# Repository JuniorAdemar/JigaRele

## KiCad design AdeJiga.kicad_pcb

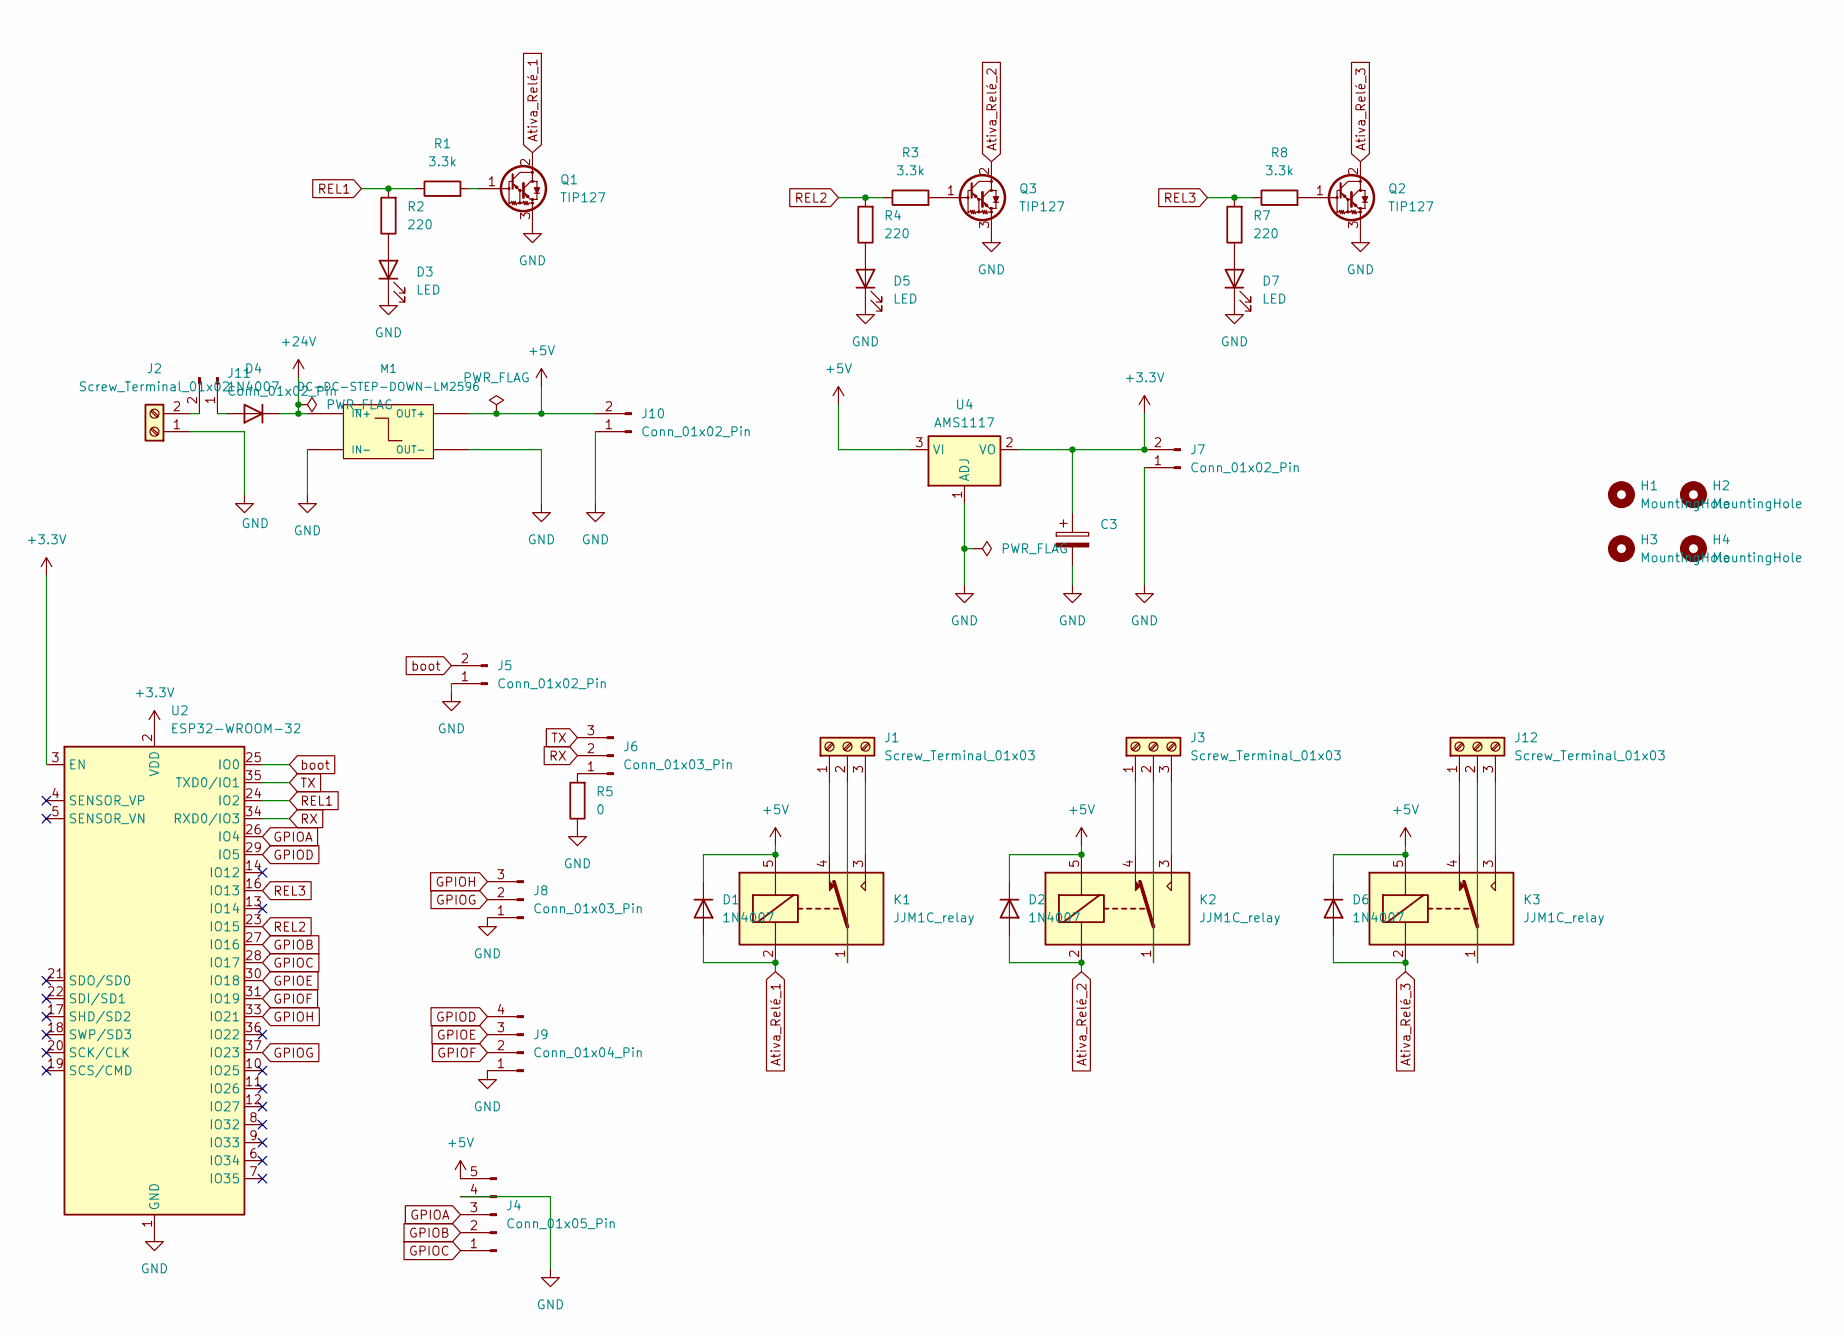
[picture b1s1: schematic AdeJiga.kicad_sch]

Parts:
C3: 220uF; CP_Radial_D6.3mm_P2.50mm
D1, D2, D4, D6: 1N4007; D_DO-41_SOD81_P10.16mm_Horizontal
D3, D5, D7: LED; LED_D5.0mm_Clear
H1, H2, H3, H4: MountingHole; MountingHole_3.2mm_M3_DIN965
J1, J3, J12: Screw_Terminal_01x03; TerminalBlock_MetzConnect_Type011_RT05503HBWC_1x03_P5.00mm_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
J2: Screw_Terminal_01x02; TerminalBlock_MetzConnect_Type011_RT05502HBWC_1x02_P5.00mm_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
J4: Conn_01x05_Pin; PinSocket_1x05_P2.54mm_Vertical
J5, J7, J10, J11: Conn_01x02_Pin; PinHeader_1x02_P2.54mm_Vertical
J6, J8: Conn_01x03_Pin; PinHeader_1x03_P2.54mm_Vertical
J9: Conn_01x04_Pin; PinHeader_1x04_P2.54mm_Vertical
K1, K2, K3: JJM1C_relay
M1: DC-DC-STEP-DOWN-LM2596
Q1, Q2, Q3: TIP127; TO-220-3_Vertical
R1, R3, R8: 3.3k; R_Axial_DIN0207_L6.3mm_D2.5mm_P10.16mm_Horizontal
R2, R4, R7: 220; R_Axial_DIN0207_L6.3mm_D2.5mm_P10.16mm_Horizontal
R5: 0; R_Axial_DIN0204_L3.6mm_D1.6mm_P5.08mm_Vertical
U2: ESP32-WROOM-32
U4: AMS1117; SOT-223-3_TabPin2

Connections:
+3.3V: C3.1, J7.2, U2.2 (VDD), U2.3 (EN), U4.2 (VO)
+5V: D1.1 (K), D2.1 (K), D6.1 (K), J4.5, J10.2, K1.5, K2.5, K3.5, M1.OUT+, U4.3 (VI)
+24V: D4.1 (K), M1.IN+
Ativa_Relé_1: D1.2 (A), K1.2, Q1.2 (C)
Ativa_Relé_2: D2.2 (A), K2.2, Q3.2 (C)
Ativa_Relé_3: D6.2 (A), K3.2, Q2.2 (C)
GND: C3.2, D3.1 (K), D5.1 (K), D7.1 (K), J2.1, J4.4, J5.1, J7.1, J8.1, J9.1, J10.1, M1.IN-, M1.OUT-, Q1.3 (E), Q2.3 (E), Q3.3 (E), R5.1, U2.1 (GND), U2.15 (GND), U2.38 (GND), U2.39 (GND), U4.1 (ADJ)
GPIOA: J4.3, U2.26 (IO4)
GPIOB: J4.2, U2.27 (IO16)
GPIOC: J4.1, U2.28 (IO17)
GPIOD: J9.4, U2.29 (IO5)
GPIOE: J9.3, U2.30 (IO18)
GPIOF: J9.2, U2.31 (IO19)
GPIOG: J8.2, U2.37 (IO23)
GPIOH: J8.3, U2.33 (IO21)
unnamed: D3.2 (A), R2.1
unnamed: D4.2 (A), J11.1
unnamed: D5.2 (A), R4.1
unnamed: D7.2 (A), R7.1
unnamed: J1.1, K1.4
unnamed: J1.2, K1.1
unnamed: J1.3, K1.3
unnamed: J3.1, K2.4
unnamed: J3.2, K2.1
unnamed: J3.3, K2.3
unnamed: J6.1, R5.2
unnamed: J2.2, J11.2
unnamed: J12.1, K3.4
unnamed: J12.2, K3.1
unnamed: J12.3, K3.3
unnamed: Q1.1 (B), R1.2
unnamed: Q2.1 (B), R8.2
unnamed: Q3.1 (B), R3.2
REL1: R1.1, R2.2, U2.24 (IO2)
REL2: R3.1, R4.2, U2.23 (IO15)
REL3: R7.2, R8.1, U2.16 (IO13)
RX: J6.2, U2.34 (RXD0/IO3)
TX: J6.3, U2.35 (TXD0/IO1)
boot: J5.2, U2.25 (IO0)

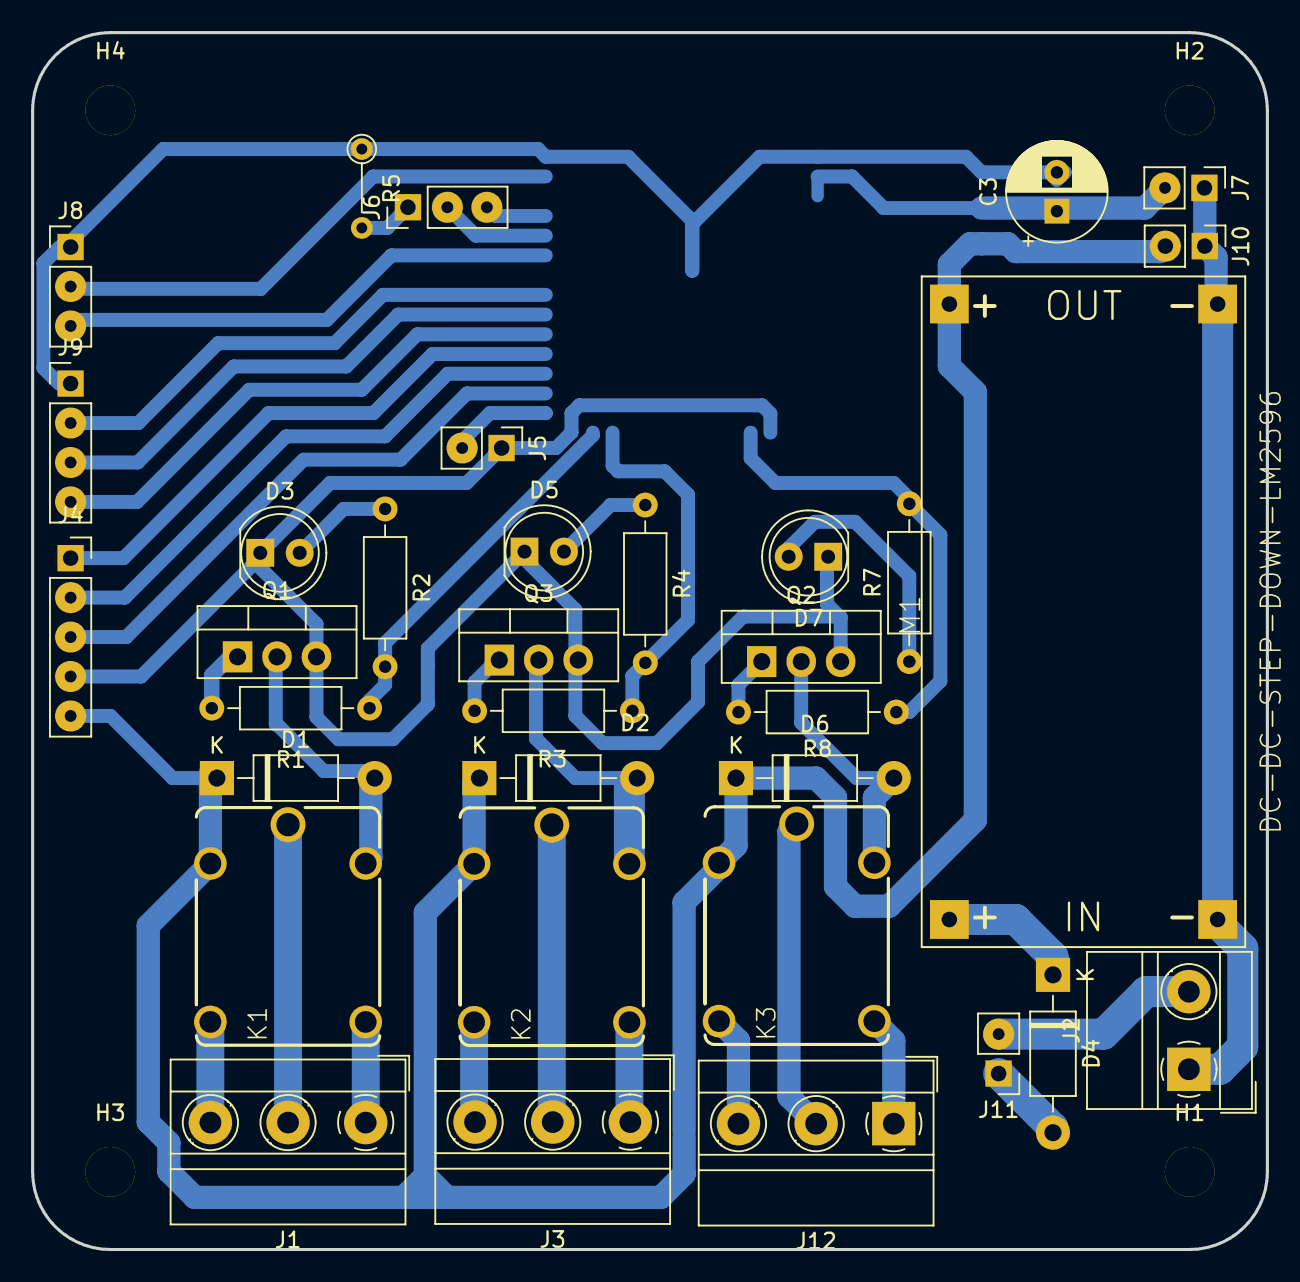
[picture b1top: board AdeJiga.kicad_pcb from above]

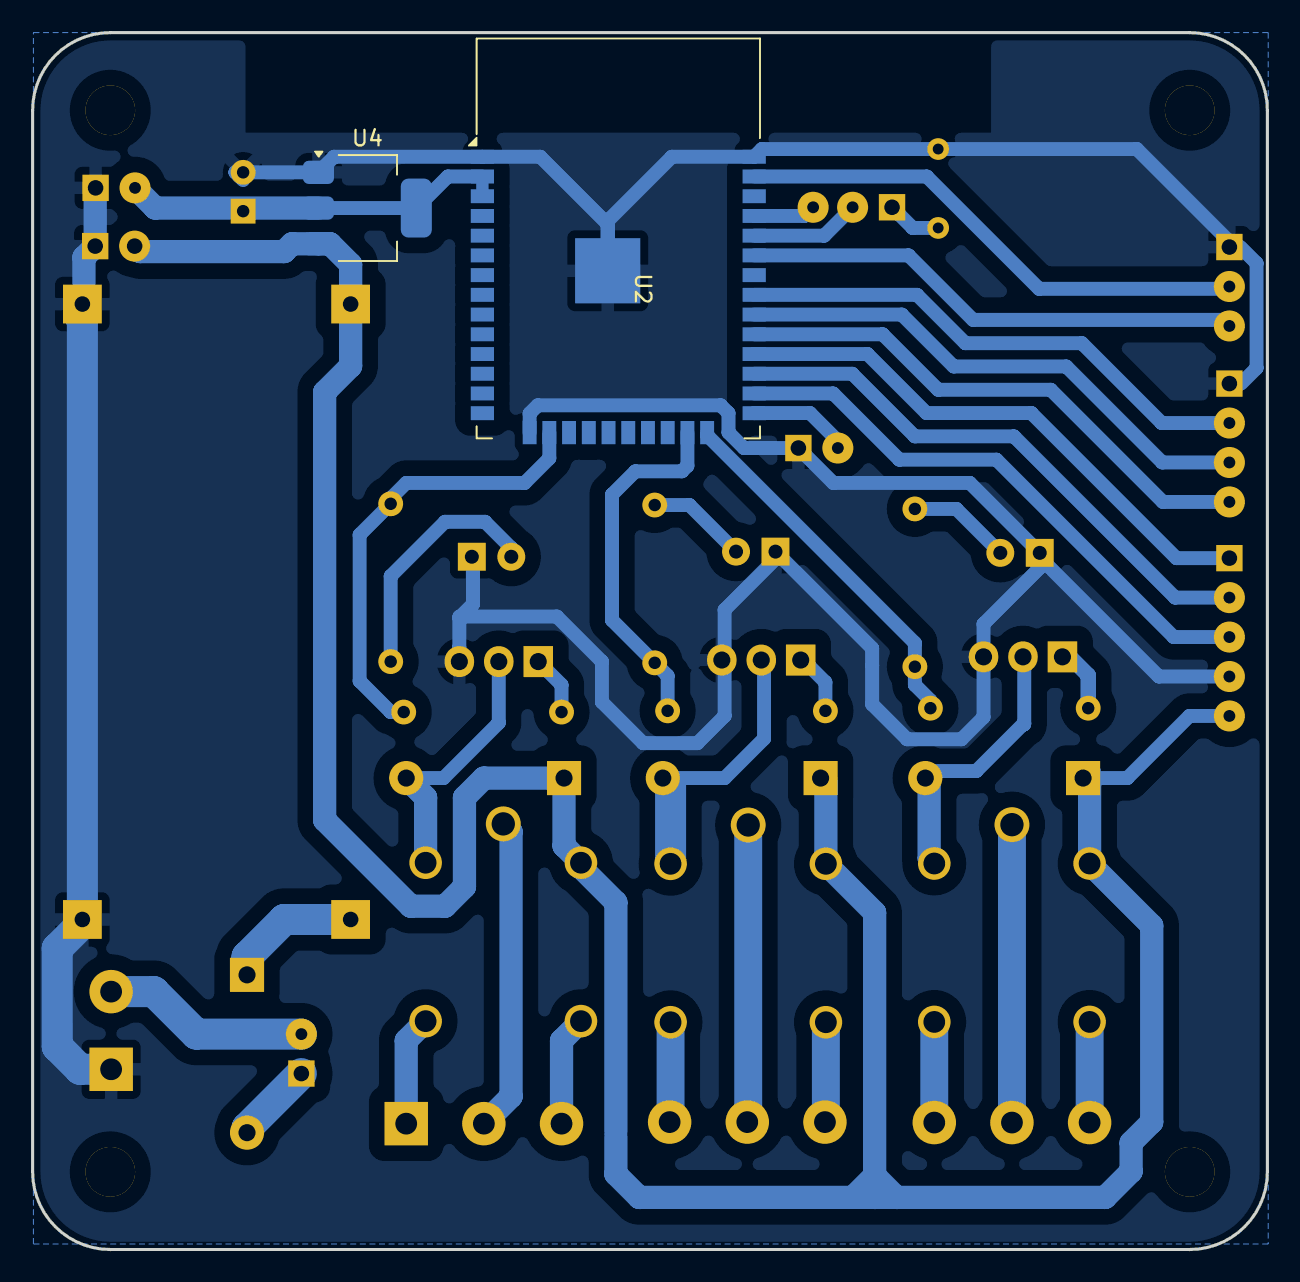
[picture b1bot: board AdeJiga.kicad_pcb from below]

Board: 2 copper layers, 79.5 x 78.3 mm, 40 parts (2 on the bottom side), 39 nets.

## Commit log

2024-09-28 primeiro commit
2024-09-30 Adicao dos modelos 3d e melhorias viasuais no layout
2024-10-04 Atualização do modelo da tampa
2024-12-06 3 reles na jiga
2024-12-11 Versão 3 consolidada, placa fabricada
2025-01-10 modificações no layout da placa e modelo 3d
2025-01-10 Algumas modificações no 3d
